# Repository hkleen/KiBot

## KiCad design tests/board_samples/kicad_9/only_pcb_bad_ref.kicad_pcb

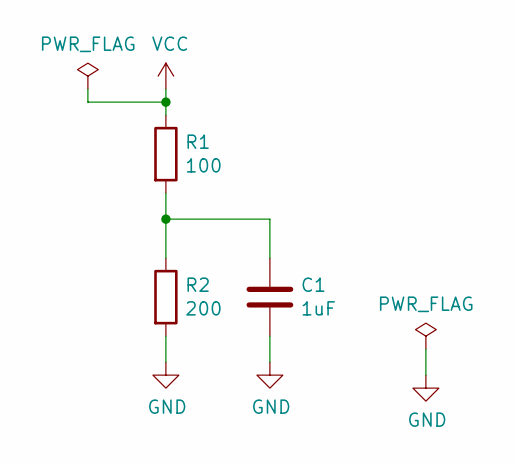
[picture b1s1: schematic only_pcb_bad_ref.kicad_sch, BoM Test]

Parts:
C1: 1uF; C_0805_2012Metric
R1: 100; R_0805_2012Metric
R2: 200; R_0805_2012Metric

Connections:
GND: C1.2, R2.2
unnamed: C1.1, R1.2, R2.1
VCC: R1.1

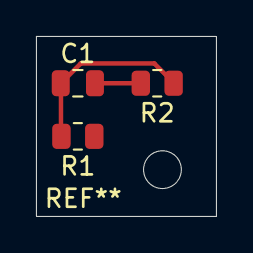
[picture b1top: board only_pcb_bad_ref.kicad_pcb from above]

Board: 2 copper layers, 10.0 x 10.0 mm, 3 parts (0 on the bottom side), 2 nets.

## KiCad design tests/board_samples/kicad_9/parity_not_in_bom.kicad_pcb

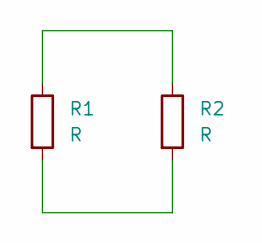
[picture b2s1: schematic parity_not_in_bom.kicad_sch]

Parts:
R1, R2: R; R_0805_2012Metric

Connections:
unnamed: R1.1, R2.1
unnamed: R1.2, R2.2

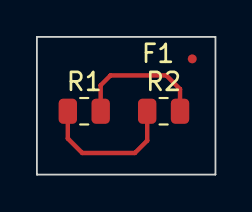
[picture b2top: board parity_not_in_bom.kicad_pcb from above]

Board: 2 copper layers, 9.9 x 7.7 mm, 3 parts (0 on the bottom side), 2 nets.

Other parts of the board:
F1: Fiducial_0.5mm_Mask1.5mm
